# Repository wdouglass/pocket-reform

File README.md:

# MNT Pocket Reform (Research Project)

## License

Copyright 2021 MNT Research GmbH.

The following licenses are used in the project, unless specified differently in a particular subfolder:

- Schematics, PCBs: [CERN-OHL-S v2](https://www.ohwr.org/project/cernohl/wikis/uploads/002d0b7d5066e6b3829168730237bddb/cern_ohl_s_v2.txt)
- Other documentation, artwork, photos and drawings that are not trademarks (see below): [CC-BY-SA 4.0](https://creativecommons.org/licenses/by-sa/4.0/legalcode)
- Software, firmware: Various. [GPL 3.0](https://www.gnu.org/licenses/gpl-3.0.en.html) if not specified otherwise in the file/subdirectory.

The "MNT" and "MNT REFORM" logos are trademarks of MNT Research GmbH. You may not use these in derived works. The reason for this is that we cannot be responsible for regulatory issues with derived boards and we cannot support them. If someone sees an MNT brand on a product, it has to be clear that it comes from MNT Research and not from a third party.

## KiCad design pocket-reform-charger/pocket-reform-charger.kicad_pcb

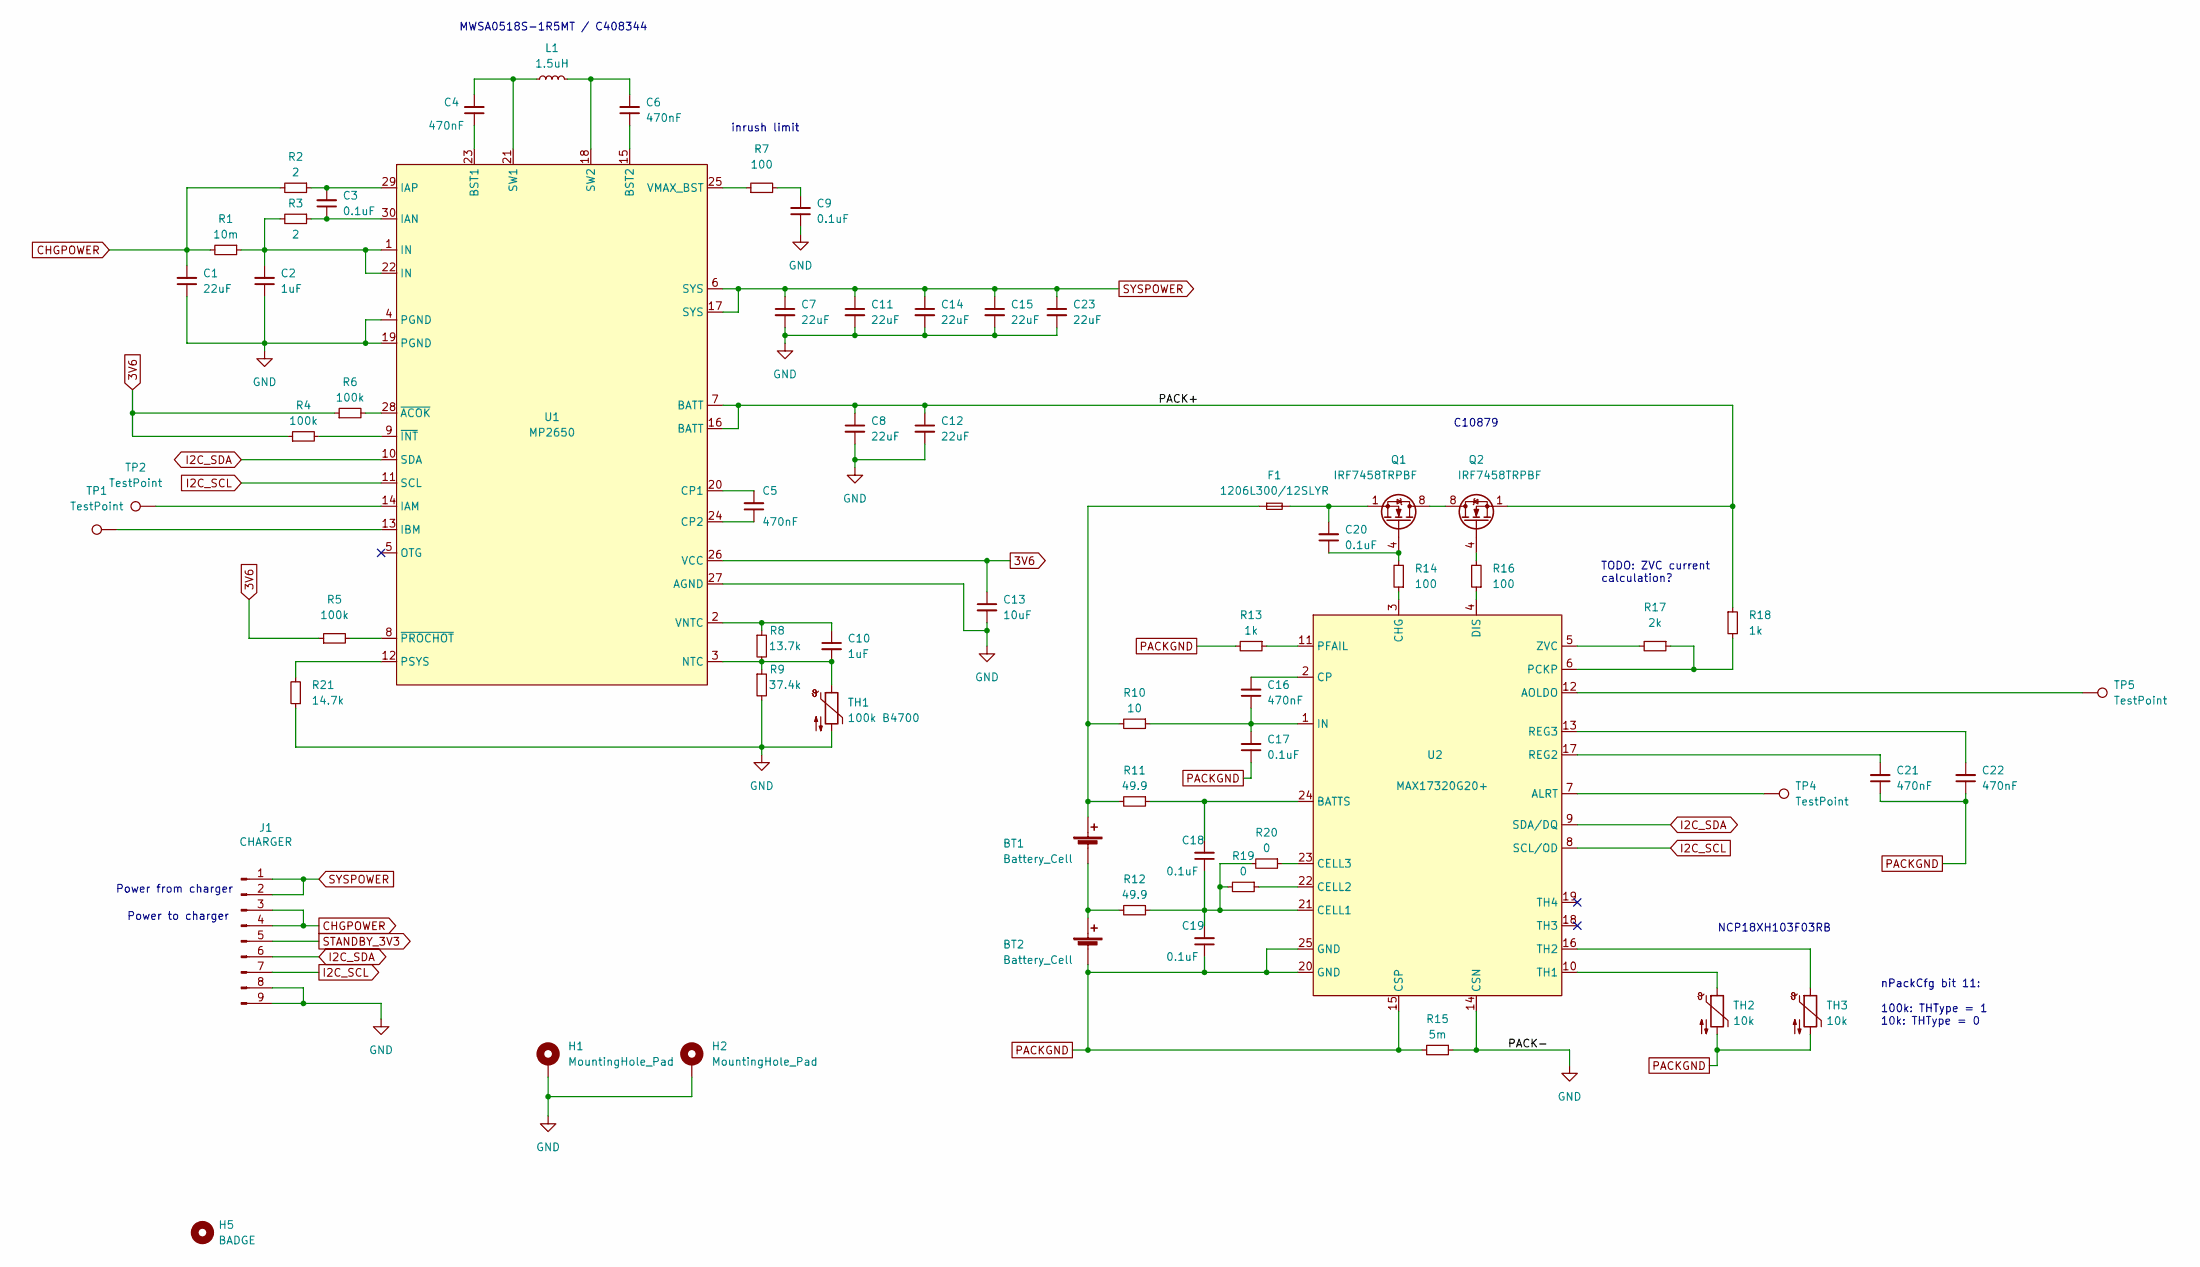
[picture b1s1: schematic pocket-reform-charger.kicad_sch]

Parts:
BT1, BT2: Battery_Cell; JST_PH_S2B-PH-SM4-TB_1x02-1MP_P2.00mm_Horizontal; LCSC C295747
C1, C7, C8, C11, C12, C14, C15, C23: 22uF; C_0805_2012Metric; LCSC C86816
C2, C10: 1uF; C_0603_1608Metric; LCSC C15849
C3, C9, C17, C18, C19, C20: 0.1uF; C_0603_1608Metric; LCSC C385964
C4, C5, C6, C16, C21, C22: 470nF; C_0603_1608Metric; LCSC C2905413
C13: 10uF; C_0603_1608Metric; LCSC C386081
F1: 1206L300/12SLYR; Fuse_1206_3216Metric; LCSC C1512043
H1, H2: MountingHole_Pad; MountingHole_2.2mm_M2_Pad
H5: BADGE; pocket-reform-charger-badge
J1: CHARGER; JST_PH_S9B-PH-SM4-TB_1x09-1MP_P2.00mm_Horizontal; LCSC C278795
L1: 1.5uH; L_Sunlord_MWSA0518_5.4x5.2mm; LCSC C408344
Q1, Q2: IRF7458TRPBF; SOIC-8_3.9x4.9mm_P1.27mm; LCSC C10879
R1: 10m; R_1206_3216Metric; LCSC C2961483
R2, R3: 2; R_0603_1608Metric; LCSC C403469
R4, R5, R6: 100k; R_0603_1608Metric; LCSC C189597
R7, R14, R16: 100; R_0603_1608Metric; LCSC C384296
R8: 13.7k; R_0603_1608Metric; LCSC C203293
R9: 37.4k; R_0603_1608Metric; LCSC C203565
R10: 10; R_0603_1608Metric; LCSC C193335
R11, R12: 49.9; R_0603_1608Metric; LCSC C403255
R13, R18: 1k; R_0603_1608Metric; LCSC C112433
R15: 5m; R_1206_3216Metric; LCSC C2937388
R17: 2k; R_0603_1608Metric; LCSC C163843
R19, R20: 0; R_0603_1608Metric
R21: 14.7k; R_0603_1608Metric; LCSC C100775
TH1: 100k B4700; R_0603_1608Metric; LCSC C153015
TH2, TH3: 10k; R_0603_1608Metric; LCSC C13564
TP1, TP2, TP4, TP5: TestPoint; TestPoint_Pad_1.0x1.0mm
U1: MP2650; MP2762A
U2: MAX17320G20+; QFN-24-1EP_4x4mm_P0.5mm_EP2.65x2.65mm_ThermalVias

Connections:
3V6: C13.1, R4.1, R5.1, R6.1, U1.26 (VCC)
/PACK+: C8.1, C12.1, Q2.1 (S), Q2.2 (S), Q2.3 (S), R18.1, U1.7 (BATT), U1.16 (BATT)
CHGPOWER: C1.2, J1.3, J1.4, R1.2, R2.2
GND: C1.1, C2.1, C7.2, C8.2, C9.1, C11.2, C12.2, C13.2, C14.2, C15.2, C23.2, H1.1, H2.1, J1.8, J1.9, R9.2, R15.1, R21.1, TH1.2, U1.4 (PGND), U1.19 (PGND), U1.27 (AGND), U2.14 (CSN)
I2C_SCL: J1.7, U1.11 (SCL), U2.8 (SCL/OD)
I2C_SDA: J1.6, U1.10 (SDA), U2.9 (SDA/DQ)
unnamed: BT1.1 (+), F1.1, R10.2, R11.2
unnamed: BT1.2 (-), BT2.1 (+), R12.2
unnamed: C2.2, R1.1, R3.2, U1.1 (IN), U1.22 (IN)
unnamed: C9.2, R7.2
unnamed: C20.2, F1.2, Q1.1 (S), Q1.2 (S), Q1.3 (S)
unnamed: Q1.5 (D), Q1.6 (D), Q1.7 (D), Q1.8 (D), Q2.5 (D), Q2.6 (D), Q2.7 (D), Q2.8 (D)
unnamed: C20.1, Q1.4 (G), R14.2
unnamed: Q2.4 (G), R16.2
unnamed: C4.1, U1.23 (BST1)
unnamed: C6.1, U1.15 (BST2)
unnamed: C5.2, U1.20 (CP1)
unnamed: C5.1, U1.24 (CP2)
unnamed: TP2.1, U1.14 (IAM)
unnamed: C3.1, R3.1, U1.30 (IAN)
unnamed: C3.2, R2.1, U1.29 (IAP)
unnamed: TP1.1, U1.13 (IBM)
unnamed: C10.2, R8.2, R9.1, TH1.1, U1.3 (NTC)
unnamed: R21.2, U1.12 (PSYS)
unnamed: C4.2, L1.1, U1.21 (SW1)
unnamed: C6.2, L1.2, U1.18 (SW2)
unnamed: R7.1, U1.25 (VMAX_BST)
unnamed: C10.1, R8.1, U1.2 (VNTC)
unnamed: R6.2, U1.28 (~ACOK)
unnamed: R4.2, U1.9 (~INT)
unnamed: R5.2, U1.8 (~PROCHOT)
unnamed: TP4.1, U2.7 (ALRT)
unnamed: TP5.1, U2.12 (AOLDO)
unnamed: C18.2, R11.1, U2.24 (BATTS)
unnamed: C18.1, C19.2, R12.1, R19.2, R20.2, U2.21 (CELL1)
unnamed: R19.1, U2.22 (CELL2)
unnamed: R20.1, U2.23 (CELL3)
unnamed: R14.1, U2.3 (CHG)
unnamed: C16.2, U2.2 (CP)
unnamed: R16.1, U2.4 (DIS)
unnamed: C16.1, C17.2, R10.1, U2.1 (IN)
unnamed: R17.1, R18.2, U2.6 (PCKP)
unnamed: R13.1, U2.11 (PFAIL)
unnamed: C21.2, U2.17 (REG2)
unnamed: C22.2, U2.13 (REG3)
unnamed: TH2.1, U2.10 (TH1)
unnamed: TH3.1, U2.16 (TH2)
unnamed: R17.2, U2.5 (ZVC)
PACKGND: BT2.2 (-), C17.1, C19.1, C21.1, C22.1, R13.2, R15.2, TH2.2, TH3.2, U2.15 (CSP), U2.20 (GND), U2.25 (GND)
STANDBY_3V3: J1.5
SYSPOWER: C7.1, C11.1, C14.1, C15.1, C23.1, J1.1, J1.2, U1.6 (SYS), U1.17 (SYS)

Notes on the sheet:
MWSA0518S-1R5MT / C408344
TODO: ZVC current calculation?
C10879
NCP18XH103F03RB
inrush limit
Power from charger
nPackCfg bit 11: 100k: THType = 1 10k: THType = 0
Power to charger

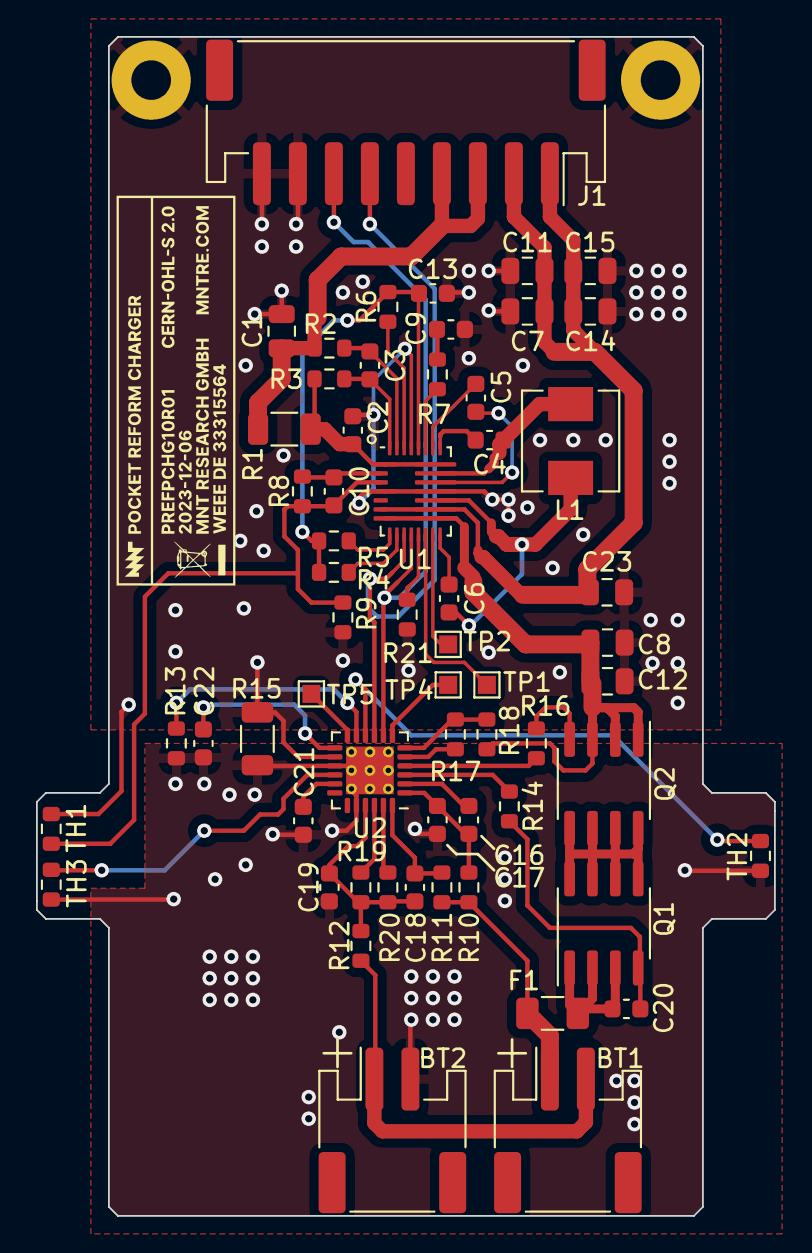
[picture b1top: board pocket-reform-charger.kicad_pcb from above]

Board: 2 copper layers, 41.0 x 65.5 mm, 63 parts (0 on the bottom side), 50 nets.

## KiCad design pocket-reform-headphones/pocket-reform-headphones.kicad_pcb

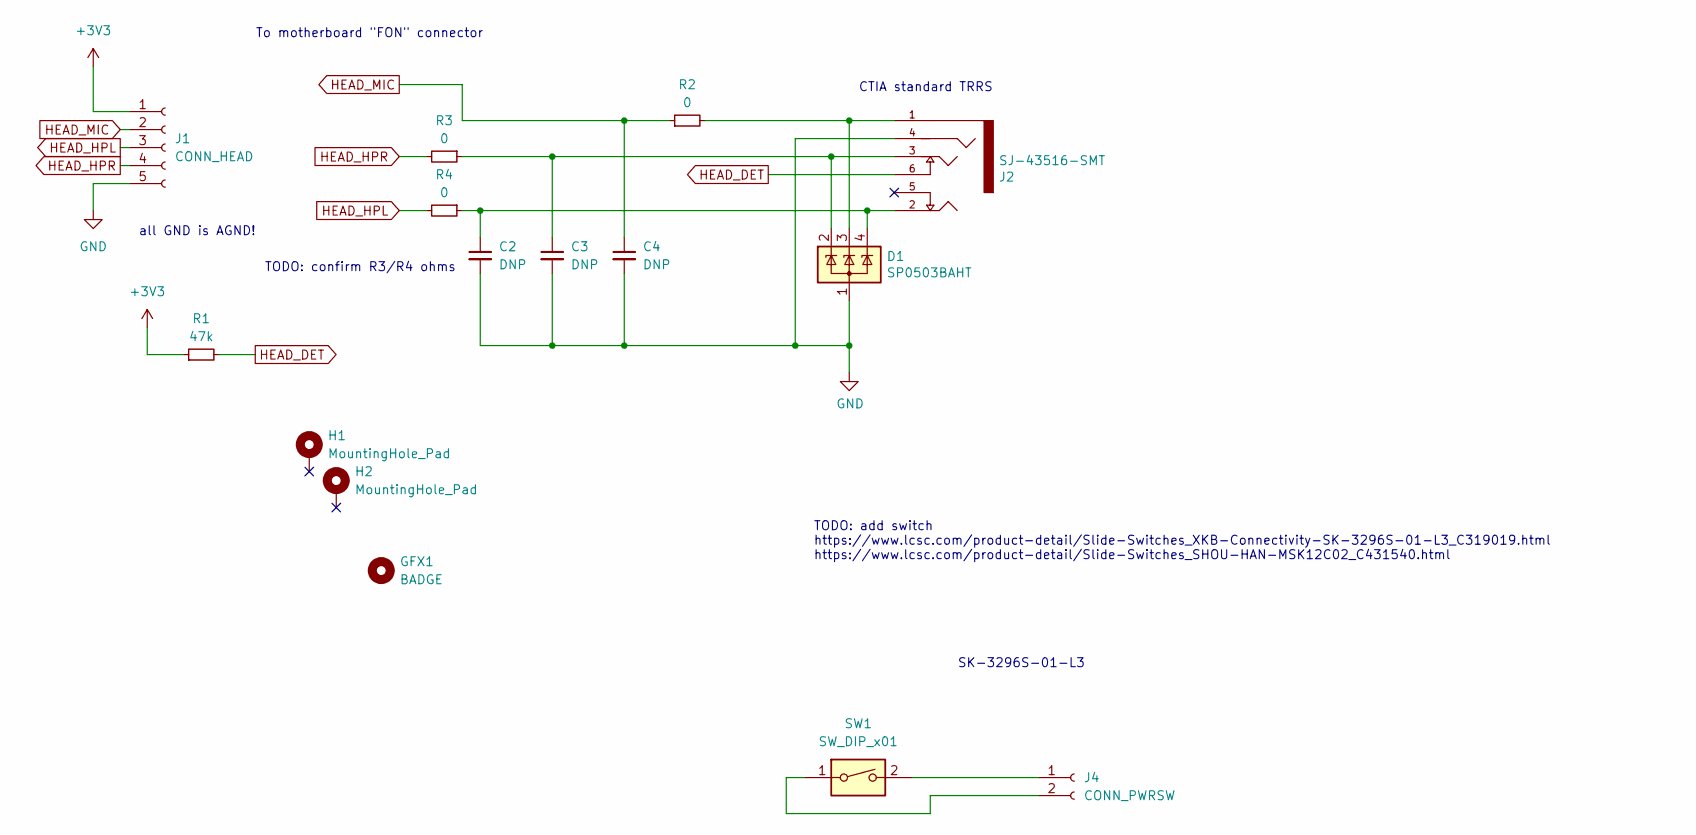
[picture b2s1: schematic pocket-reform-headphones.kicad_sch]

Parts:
C2, C3, C4: DNP; C_0603_1608Metric; LCSC DNP
D1: SP0503BAHT; SOT-143; LCSC C3040626
GFX1: BADGE; pref-headset-badge
H1, H2: MountingHole_Pad; MountingHole_2.2mm_M2_DIN965_Pad
J1: CONN_HEAD; JST_SH_SM05B-SRSS-TB_1x05-1MP_P1.00mm_Horizontal; LCSC C136657
J2: SJ-43516-SMT
J4: CONN_PWRSW; JST_SH_SM02B-SRSS-TB_1x02-1MP_P1.00mm_Horizontal; LCSC C160402
R1: 47k; R_0603_1608Metric
R2, R3, R4: 0; R_0603_1608Metric
SW1: SW_DIP_x01; SW_SPDT_PCM12; LCSC C319019

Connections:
+3V3: J1.1, R1.1
GND: C2.2, C3.2, C4.2, D1.1 (A), J1.5, J2.4 (RING2)
HEAD_DET: J2.6 (RING_SWITCH), R1.2
HEAD_HPL: J1.3, R4.2
HEAD_HPR: J1.4, R3.2
HEAD_MIC: C4.1, J1.2, R2.1
unnamed: C3.1, D1.2 (K), J2.3 (RING1), R3.1
unnamed: D1.3 (K), J2.1 (SLEEVE), R2.2
unnamed: C2.1, D1.4 (K), J2.2 (TIP), R4.1
unnamed: J4.1, SW1.2
unnamed: J4.2, SW1.1

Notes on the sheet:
SK-3296S-01-L3
To motherboard "FON" connector
TODO: add switch https://www.lcsc.com/product-detail/Slide-Switches_XKB-Connectivity-SK-3296S-01-L3_C319019.html https://www.lcsc.com/product-detail/Slide-Switches_SHOU-HAN-MSK12C02_C431540.html
all GND is AGND!
CTIA standard TRRS
TODO: confirm R3/R4 ohms

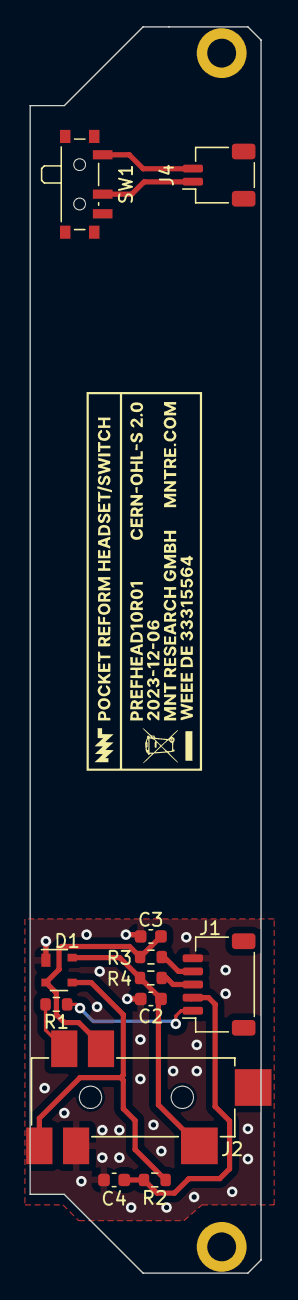
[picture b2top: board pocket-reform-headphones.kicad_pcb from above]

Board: 2 copper layers, 17.6 x 95.0 mm, 15 parts (0 on the bottom side), 11 nets.

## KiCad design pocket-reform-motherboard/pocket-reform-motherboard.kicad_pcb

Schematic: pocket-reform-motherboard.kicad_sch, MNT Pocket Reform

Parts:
BT1: V364; BatteryHolder_Keystone_2998_1x6.8mm
C2, C4, C5, C6, C17, C39, C51, C56, C65, C67: 10uF; C_0603_1608Metric
C7, C8, C11, C12, C18, C19, C52, C58: 10nF; C_0603_1608Metric
C9, C10, C20, C26, C34, C36: 1uF; C_0603_1608Metric
C13: 12pF; C_0603_1608Metric
C14, C83, C123, C124, C126: 47uF; C_0603_1608Metric
C15, C16: 330uF; CP_Elec_6.3x5.4
C21, C23: 18pF; C_0603_1608Metric
C22, C24: 27pF; C_0603_1608Metric; LCSC C107045
C25, C27, C28, C29, C30, C31, C32, C33, C35, C38, C40, C41, C42, C43, C44, C45, C46, C47, C48, C49, C50, C53, C54, C55, C57, C59, C60, C61, C62, C63, C64, C66, C68, C69, C72, C73, C76, C77, C78, C85, C86, C87, C88, C89, C90, C91, C92, C93: 0.1uF; C_0603_1608Metric
C37: 1nF; C_0603_1608Metric
C82: 470nF; C_0603_1608Metric
D1: LED_MODEM; LED_0603_1608Metric
D2, D4, D5, D6: PMEG3050EP,115; D_SOD-128
D7: BZX84-C5V6,215; D_SOD-323
D8, D9: LED_Small; LED_0603_1608Metric
D10: 19-337/R6GHBHC-A01/2T; LED_19-337_R6GHBHC-A01_2T
D11: SS54?; D_SMA
D12: SD0603S040S0R2; D_0603_1608Metric
D23: LED_NVME; LED_0603_1608Metric
FB1: 220@100MHz 1.4A; L_0603_1608Metric
FB2, FB3, FB4, FB5, FB8, FB9, FB10: 100@100MHz 3A; L_0603_1608Metric
GFX1: MountingHole; pocket-reform
H1, H2, H3, H4: MountingHole_Pad; MountingHole_2.2mm_M2_DIN965_Pad
H5, H6, H7: NGFF-Mount1; WA-SMSI-M2
J1: CHARGER; JST_PH_S9B-PH-SM4-TB_1x09-1MP_P2.00mm_Horizontal
J2: DM3AT-SF-PEJM5; LCSC C114218
J3, J14: USB_C_Receptacle; USB_C_Receptacle_Amphenol_12401548E4-2A_CircularHoles
J4: 09452812561; Manufacturer_Part_Number 09452812561; Mouser Part Number 617-09452812561
J5: SYSCTL; JST_PH_S4B-PH-SM4-TB_1x04-1MP_P2.00mm_Horizontal
J6: USB_INT1; JST_PH_S4B-PH-SM4-TB_1x04-1MP_P2.00mm_Horizontal
J7: HDMI_D_1.4; HDMI_Micro-D_Molex_46765-0x01
J8: SIM_Card; MOLEX_78800-0001
J9: USB_C_Receptacle_USB2.0; USB_C_Receptacle_HRO_TYPE-C-31-M-12
J10: 1-2199230-6; TE_1-2199230-6
J11: Conn_01x33; Hirose_FH12-33S-0.5SH_1x33-1MP_P0.50mm_Horizontal
J12: 2199230-5; TE_2199230-5
J13: FH35C-31S-0.3HW(50); TE_3-2328724-1
J15: Conn_01x02; JST_GH_SM02B-GHS-TB_1x02-1MP_P1.25mm_Horizontal
J16, J17: Conn_01x03; PinHeader_1x03_P2.54mm_Vertical
L1: 22uH; L_Taiyo-Yuden_NR-30xx
L2: 2.2uH; L_1210_3225Metric
L3, L4: 15uH; L_Vishay_IHLP-4040
L5, L6: 15uH; L_Taiyo-Yuden_NR-30xx; LCSC C223122
MK1: MP23ABS1TR; MIC_MP23ABS1TR; PARTREV 5
R1, R29, R34, R36, R58, R60, R61, R110: 1k; R_0603_1608Metric
R4, R5, R9, R11, R12, R13, R44, R45, R46, R49, R50, R51, R67, R70, R71, R81, R83, R84, R101, R102, R103, R104, R105, R106, R107, R108, R109, R111: 0; R_0603_1608Metric
R6, R7, R8, R69, R87: 100k; R_0603_1608Metric
R10, R27, R55: 200k; R_0603_1608Metric
R14: 280k; R_0603_1608Metric
R15, R17, R22, R30, R32, R38, R52, R54, R56, R68, R75, R85, R96: 10k; R_0603_1608Metric
R16: 3.16k; R_0603_1608Metric
R18: 5.83k; R_0603_1608Metric
R19: 1.3M; R_0603_1608Metric
R20: 300k; R_0603_1608Metric
R21: 1M; R_0603_1608Metric
R23, R62, R63, R64: DNP; R_0603_1608Metric
R24, R25, R26, R89, R93: 4.7k; R_0603_1608Metric
R28: 120k; R_0603_1608Metric
R31, R33: 36k; R_0603_1608Metric
R35: 1k; R_0603_1608Metric; LCSC C105428
R37, R39, R40, R41: 75 1%; R_0603_1608Metric
R47, R48: 27.4; R_0603_1608Metric
R53: 12k 1%; R_0603_1608Metric
R57, R59: 4.7k; R_0603_1608Metric; LCSC C105428
R65, R66, R198, R199: 49.9; R_0603_1608Metric
R72: 2k2; R_0603_1608Metric
R76, R77, R79, R80, R82: 33; R_0603_1608Metric
R90: 27k; R_0603_1608Metric
R97, R98, R99, R100: 47k; R_0603_1608Metric
SW1: SW_DIP_x01; SW_DIP_SPSTx01_Slide_Omron_A6S-110x_W8.9mm_P2.54mm
SW2: RESET; SW_Push_1P1T_NO_CK_KMR2
TP1: PRTCTL1; TestPoint_Pad_D1.0mm
TP2: PRTCTL3; TestPoint_Pad_D1.0mm
TP3: PRTCTL2; TestPoint_Pad_D1.0mm
TP4: PRTCTL4; TestPoint_Pad_D1.0mm
TP5, TP6: TestPoint; TestPoint_Pad_D1.0mm; LCSC DNP
TR1: TG111-MSC13LF; Transformer_Ethernet_HALO_TG111-MSC13
U1: reform2-som-connector; TE_1473149-4
U2: MAX1837EUT33+T; SOT-23-6
U3: LM3674MFX-ADJ/NOPB; SOT-23-5
U4: TLV1117-18; SOT-223
U5, U6: TPS5450DDAR; TI_SO-PowerPAD-8_ThermalVias
U7: CN301; SOT-23-5
U8: RP2040; RP2040-QFN-56
U9: USB7002/KDX; QFN40P1200X1200X90-101N; PARTREV N/A
U10: W25Q32JVSS; SOIC-8_5.23x5.23mm_P1.27mm
U11: PCF8523T; SOIC-8_3.9x4.9mm_P1.27mm
U12: AP22815; SOT-23-5
U13: TXS0108EPW; TSSOP-20_4.4x6.5mm_P0.65mm
U14: SN74AVC1T45; SOT-23-6
U15, U16, U19, U20, U21, U22: TPD4E02B04DQA; USON-10_2.5x1.0mm_P0.5mm
U17: TPD12S521; TSSOP50P640X120-38N
U18: TLV320AIC3100; VQFN-32-1EP_5x5mm_P0.5mm_EP3.5x3.5mm
U23: FUSB302BMPX; WQFN-14-1EP_2.5x2.5mm_P0.5mm_EP1.45x1.45mm
Y1: 25MHz; Crystal_SMD_Abracon_ABM8G-4Pin_3.2x2.5mm
Y2: 12MHz 18pF; Crystal_SMD_3225-4Pin_3.2x2.5mm; LCSC C91749
Y3: 32.768 kHz; Crystal_SMD_3215-2Pin_3.2x1.5mm

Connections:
1V2_ENABLE: R8.1, R46.2, U3.3 (EN)
3V3_ENABLE: R7.1, R49.2, U6.5 (EN)
5V_ENABLE: R6.1, R51.2, U5.5 (EN)
+1V1: C26.1, C28.1, C30.1, U8.23 (DVDD), U8.45 (VREG_VOUT), U8.50 (DVDD)
+1V2: C13.1, C17.1, L2.2, R14.1, U9.9 (VDD12), U9.18 (VDD12), U9.25 (VDD12), U9.33 (VDD12), U9.41 (VDD12), U9.55 (VDD12), U9.78 (VDD12), U9.83 (VDD12), U9.93 (VDD12)
+1V8: C10.1, C56.1, C62.1, J13.31, R71.2, R81.2, U4.2 (VO), U18.3 (DVDD)
+3V3: C6.1, C16.1, C19.2, C69.2, C77.1, FB3.1, FB4.1, FB5.2, FB8.1, J13.1, J13.2, J13.3, J13.4, J13.26, J13.27, L4.2, MK1.5 (VDD), R4.2, R17.1, R22.1, R25.1, R29.1, R30.1, R31.1, R32.1, R33.1, R34.1, R52.2, R54.2, R85.1, R87.1, R90.1, R97.2, R98.2, R99.2, R100.2, U3.1 (Vin), U9.26 (VDD33), U9.44 (VDD33), U9.53 (VDD33), U9.62 (VDD33), U9.67 (VDD33), U9.79 (VDD33), U9.86 (VDD33), U9.99 (VDD33)
+5V: C15.1, C18.2, C40.1, C47.1, C73.2, D12.2 (A), FB1.1, FB2.1, J3.A4 (VBUS), J3.A9 (VBUS), J3.B4 (VBUS), J3.B9 (VBUS), L3.2, R11.1, R15.1, R62.2, R68.2, U1.1 (5V), U1.2 (5V), U1.3 (5V), U1.4 (5V), U1.5 (5V), U1.6 (5V), U8.48 (USB_VDD), U12.5 (IN), U17.1 (5V_SUPPLY)
/DP1_DISCHARGE: U9.46 (PF5)
/DP1_VCONN1: U9.49 (PF8)
/DP1_VCONN2: U9.50 (PF9)
/DP2_DISCHARGE: U9.45 (PF4)
/DP2_VCONN1: U9.51 (PF10)
/DP2_VCONN2: U9.52 (PF11)
/GPIO90: U9.75 (PF26)
/GPIO91: U9.76 (PF27)
/GPIO92: U9.77 (PF28)
/GPIO93: U9.74 (PF29)
/GPIO94: R54.1, U9.2 (PF30/VBUS_DET)
/GPIO95: U9.3 (PF31)
/M2_CLKREQn: J10.52
/M2_SMB_ALERTn: J10.44
/M2_SMB_CLK: J10.40
/M2_SMB_DATA: J10.42
/M_ANTCTL0: J12.59
/M_ANTCTL1: J12.61
/M_ANTCTL2: J12.58
/M_ANTCTL3: J12.56
/M_COEX1: J12.64
/M_COEX2: J12.62
/M_CONFIG_0: J12.21
/M_CONFIG_1: J12.69
/M_CONFIG_2: J12.75
/M_CONFIG_3: J12.1
/M_DPR: J12.25
/M_I2C_SCL: J12.38
/M_I2C_SDA: J12.68
/M_I2S_CLK: J12.20
/M_I2S_MCLK(IO): J12.60
/M_I2S_RX: J12.22
/M_I2S_TX: J12.24
/M_I2S_WA: J12.28
/M_LAA_TX_EN: J12.63
/M_SIM1_DET: J12.66
/M_SIM2_CLK: J12.44
/M_SIM2_DATA: J12.42
/M_SIM2_DET: J12.40
/M_SIM2_PWR: J12.48
/M_SIM2_RESET: J12.46
/M_VIO_1V8: J12.65
/PRT_CTL1: TP1.1, U9.60 (PF17)
/PRT_CTL2: TP3.1, U9.58 (PF15)
/PRT_CTL3: TP2.1, U9.59 (PF16)
/PRT_CTL4: TP4.1, U9.56 (PF13)
/RUD+: J9.A6 (D+), J9.B6 (D+), R47.2, R63.1
/RUD-: J9.A7 (D-), J9.B7 (D-), R48.2, R64.1
/U_GPIO70: U9.47 (PF6)
/U_GPIO71: U9.48 (PF7)
/U_GPIO76: U9.54 (PF12)
/U_GPIO78: U9.57 (PF14)
/U_M_I2C_CLK: U9.61 (PF18)
/U_M_I2C_DATA: U9.66 (PF19)
/U_SPI_CE_N: U9.69 (PF20/CFG_NON_REM)
/U_SPI_CLK: U9.68 (PF21)
/U_SPI_D0: R55.1, U9.70 (PF22/CFG_BC_EN)
/U_SPI_D1: U9.71 (PF23)
/U_SPI_D2: U9.72 (PF24)
/U_SPI_D3: U9.73 (PF25)
/~M_LED1: D1.1 (K), J12.10
/~M_PWROFF: J12.6
/~M_WOWWAN: J12.23
/~M_W_DISABLE1: J12.8
/~M_W_DISABLE2: J12.26
/~PCIE2_CLKREQ: J12.52
/~PCIE2_WAKE: J12.54
BACKLIGHT_EN: J13.6
BACKLIGHT_PWM: U1.164 (SPDIF_RX/PWM2)
DAC_BCLK: R76.1, U1.170 (SAI2_TXC)
DAC_DIN: R79.1, U1.166 (SAI2_RXD)
DAC_DOUT: R77.1, U1.178 (SAI2_TXD)
DAC_MCLK: R82.2, U1.176 (SAI2_MCLK)
DAC_RXFS: U1.168 (SAI2_RXFS)
DAC_SCL: U1.101 (I2C3_SCL), U11.6 (SCL), U18.10 (SCL)
DAC_SDA: U1.103 (I2C3_SDA), U11.5 (SDA), U18.9 (SDA)
DAC_TXFS: R80.1, U1.172 (SAI2_TXFS)
DISP_EN: J13.30
DISP_TE: J13.25
DSI_CLK_N: J11.19, J13.15
DSI_CLK_P: J11.20, J13.16
DSI_D0_N: J11.25, J13.12
DSI_D0_P: J11.26, J13.13
DSI_D1_N: J11.22, J13.18
DSI_D1_P: J11.23, J13.19
DSI_D2_N: J11.16, J13.21
DSI_D2_P: J11.17, J13.22
DSI_D3_N: J11.13, J13.9
DSI_D3_P: J11.14, J13.10
ETH0_A+: TR1.2 (TD1+), U1.29 (TRX0_P)
ETH0_A-: TR1.3 (TD1-), U1.27 (TRX0_N)
ETH0_B+: TR1.5 (TD2+), U1.23 (TRX1_P)
ETH0_B-: TR1.6 (TD2-), U1.21 (TRX1_N)
ETH0_C+: TR1.8 (TD3+), U1.17 (TRX2_P)
ETH0_C-: TR1.9 (TD3-), U1.15 (TRX2_N)
ETH0_D+: TR1.11 (TD4+), U1.11 (TRX3_P)
ETH0_D-: TR1.12 (TD4-), U1.9 (TRX3_N)
ETH0_DA+: J4.1, TR1.23 (MTX1+)
ETH0_DA-: J4.2, TR1.22 (MTX1-)
ETH0_DB+: J4.6, TR1.20 (MTX2+)
ETH0_DB-: J4.7, TR1.19 (MTX2-)
ETH0_DC+: J4.4, TR1.17 (MTX3+)
ETH0_DC-: J4.5, TR1.16 (MTX3-)
ETH0_DD+: J4.9, TR1.14 (MX4+)
ETH0_DD-: J4.10, TR1.13 (MX4-)
ETH0_LED_LINK1: D9.1 (K), U1.83 (JTAG_TDO)
ETH0_LED_RX: D8.1 (K), U1.79 (JTAG_MOD)
HDMI_AUXN: U1.189 (HDMI_AUX_N)
HDMI_AUXP: U1.187 (HDMI_AUX_P)
HDMI_CEC: R100.1, U1.197 (HDMI_CEC), U17.16 (CE_REMOTE_IN)
HDMI_CLKN: J7.14 (CK-), U1.163 (HDMI_CLK_N), U17.15 (TMDS_CK-), U17.24 (TMDS_CK-)
HDMI_CLKP: J7.12 (CK+), U1.165 (HDMI_CLK_P), U17.13 (TMDS_CK+), U17.26 (TMDS_CK+)
HDMI_HPD: R97.1, U1.199 (HDMI_HPD), U17.19 (HOTPLUG_DET_IN)
HDMI_SCL: R98.1, U1.195 (HDMI_DDC_SCL), U17.17 (DDC_CLK_IN)
HDMI_SDA: R99.1, U1.193 (HDMI_DDC_SDA), U17.18 (DDC_DAT_IN)
HDMI_TX0N: J7.11 (D0-), U1.169 (HDMI_TX0_N), U17.12 (TMDS_D0-), U17.27 (TMDS_D0-)
HDMI_TX0P: J7.9 (D0+), U1.171 (HDMI_TX0_P), U17.10 (TMDS_D0+), U17.29 (TMDS_D0+)
HDMI_TX1N: J7.8 (D1-), U1.175 (HDMI_TX1_N), U17.9 (TMDS_D1-), U17.30 (TMDS_D1-)
HDMI_TX1P: J7.6 (D1+), U1.177 (HDMI_TX1_P), U17.7 (TMDS_D1+), U17.32 (TMDS_D1+)
HDMI_TX2N: J7.5 (D2-), U1.181 (HDMI_TX2_N), U17.6 (TMDS_D2-), U17.33 (TMDS_D2-)
HDMI_TX2P: J7.3 (D2+), U1.183 (HDMI_TX2_P), U17.4 (TMDS_D2+), U17.35 (TMDS_D2+)
IMX_RESETn: U1.87 (EXT_RESET_N)
IMX_RTC_IRQ: R67.1, U1.141 (RTC_IRQ)
IMX_UART1_RX: J16.2, U1.126 (UART1_RXD)
IMX_UART1_TX: J16.1, U1.128 (UART1_TXD)
IMX_UART2_RX: J17.2, U1.122 (UART2_RXD)
IMX_UART2_TX: J17.1, U1.124 (UART2_TXD)
IMX_WAKE: R45.2, U1.145 (GPIO1_IO3)
LPC_MISO: R50.2, U1.93 (ECSPI2_MISO)
LPC_MOSI: R44.2, U1.91 (ECSPI2_MOSI)
LPC_SCK: U1.97 (ECSPI2_SCLK), U8.13 (GPIO10)
LPC_SS0: U1.89 (ECSPI2_SS0), U8.12 (GPIO9)
M2B_RST: J12.67
unnamed: BT1.1 (+), U11.3 (VBAT)
unnamed: C9.1, R4.1, U4.3 (VI)
unnamed: C11.1, U5.1 (BOOT)
unnamed: C11.2, D5.1 (K), L3.1, U5.8 (PH)
unnamed: C12.1, U6.1 (BOOT)
unnamed: C12.2, D6.1 (K), L4.1, U6.8 (PH)
unnamed: C13.2, R10.1, R14.2, U3.4 (FB)
unnamed: C20.1, D7.1 (K), R21.1, U7.2 (VCC)
unnamed: C21.1, U9.97 (XTALO), Y1.1
unnamed: C22.1, U8.20 (XIN), Y2.1
unnamed: C23.1, U9.98 (XTALI/CLK_IN), Y1.3
unnamed: C24.1, R35.1, Y2.3
unnamed: C37.1, R37.2, R39.2, R40.2, R41.2
unnamed: C39.1, C41.1, FB1.2, J6.1
unnamed: C42.1, TR1.1 (TCT1)
unnamed: C43.1, TR1.4 (TCT2)
unnamed: C44.1, TR1.7 (TCT3)
unnamed: C45.1, TR1.10 (TCT4)
unnamed: C48.1, C49.1, R75.1, R81.1, U13.2 (VCCA), U14.1 (VCCA)
unnamed: C50.1, C51.1, FB5.1, U18.17 (AVDD), U18.28 (HPVDD)
unnamed: C57.1, C67.1, FB2.2, U18.21 (SPKVDD), U18.24 (SPKVDD)
unnamed: C63.1, C64.1, C65.1, C66.1, FB8.2, J2.4 (VDD), U13.19 (VCCB), U14.6 (VCCB)
unnamed: C68.1, U18.14 (MIC1RP)
unnamed: C68.2, MK1.1 (OUT), R72.2, U18.11 (VOL/MICDET)
unnamed: C72.2, U17.37 (ESD_BYP)
unnamed: C76.1, C82.1, J15.1, L5.2
unnamed: C78.1, C82.2, J15.2, L6.2
unnamed: C85.1, J3.A3 (TX1-), U20.4 (IO3)
unnamed: C86.1, J3.B3 (TX2-), U22.4 (IO3)
unnamed: C87.1, J7.19 (+5V), U17.38 (5V_OUT)
unnamed: C88.1, J3.A2 (TX1+), U20.5 (IO4)
unnamed: C89.1, J3.B2 (TX2+), U22.5 (IO4)
unnamed: C90.1, J14.A3 (TX1-), U19.4 (IO3)
unnamed: C91.1, J14.B3 (TX2-), U21.4 (IO3)
unnamed: C92.1, J14.A2 (TX1+), U19.5 (IO4)
unnamed: C93.1, J14.B2 (TX2+), U21.5 (IO4)
unnamed: C52.1, C53.1, C54.1, C55.1, C83.1, C123.1, FB3.2, J12.2, J12.4, J12.70, J12.72, J12.74, R1.1
unnamed: C58.1, C59.1, C60.1, C61.1, C124.1, C126.1, FB4.2, J10.2, J10.4, J10.12, J10.14, J10.16, J10.18, J10.70, J10.72, J10.74, R110.1
unnamed: D1.2 (A), R1.2
unnamed: D4.1 (K), L1.1, U2.4 (LX)
unnamed: D8.2 (A), R29.2
unnamed: D9.2 (A), R34.2
unnamed: D10.4 (BA), R61.2
unnamed: D10.5 (GA), R60.2
unnamed: D10.6 (RA), R58.2
unnamed: D12.1 (K), R89.1, R93.1
unnamed: D23.1 (K), J10.10
unnamed: D23.2 (A), R110.2
unnamed: FB9.1, U18.22 (SPKP), U18.26 (SPKP)
unnamed: FB9.2, L5.1
unnamed: FB10.1, U18.19 (SPKM), U18.23 (SPKM)
unnamed: FB10.2, L6.1
unnamed: J2.1 (DAT2), U13.20 (B1)
unnamed: J2.2 (DAT3/CD), U13.18 (B2)
unnamed: J2.3 (CMD), U13.14 (B6)
unnamed: J2.5 (CLK), U14.4 (B)
unnamed: J2.7 (DAT0), U13.13 (B7)
unnamed: J2.8 (DAT1), U13.12 (B8)
unnamed: J3.A5 (CC1), R83.1, U16.1 (IO1)
unnamed: J3.B5 (CC2), R84.1, U16.2 (IO2)
unnamed: J7.1 (HPD/HEAC-), R96.1, U17.20 (HOTPLUG_DET_OUT)
unnamed: J7.15 (CEC), R90.2, U17.23 (CE_REMOTE_OUT)
unnamed: J7.17 (SCL), R89.2, U17.22 (DDC_CLK_OUT)
unnamed: J7.18 (SDA), R93.2, U17.21 (DDC_DAT_OUT)
unnamed: J9.A4 (VBUS), J9.A9 (VBUS), J9.B4 (VBUS), J9.B9 (VBUS), R62.1
unnamed: J10.11, R107.1
unnamed: J10.13, R104.1
unnamed: J10.23, R108.1
unnamed: J10.25, R105.1
unnamed: J10.35, R109.1
unnamed: J10.37, R106.1
unnamed: J14.A5 (CC1), R101.2, R111.1, U15.1 (IO1)
unnamed: J14.B5 (CC2), R102.2, R103.1, U15.2 (IO2)
unnamed: L2.1, U3.5 (SW)
unnamed: R5.1, U9.1 (RESET_N)
unnamed: R9.1, U2.1 (FB)
unnamed: R11.2, U1.118 (USB1_VBUS)
unnamed: R12.2, U1.30 (UART3_TXD)
unnamed: R13.1, U1.32 (UART3_RXD)
unnamed: R15.2, R16.1, U5.4 (VSENSE)
unnamed: R17.2, R18.1, U6.4 (VSENSE)
unnamed: R19.1, R20.2, U7.4 (LBI)
unnamed: R22.2, R23.1, U9.21 (CFG_STRAP1)
unnamed: R24.1, U9.64 (TEST2)
unnamed: R25.2, U9.63 (TEST1)
unnamed: R26.1, U9.65 (TEST3)
unnamed: R27.1, U9.22 (CFG_STRAP2)
unnamed: R30.2, U9.4 (DP1_VBUS_MON)
unnamed: R31.2, U9.87 (CC1_UP)
unnamed: R32.2, U9.36 (DP2_VBUS_MON)
unnamed: R33.2, U9.88 (CC2_UP)
unnamed: R35.2, U8.21 (XOUT)
unnamed: R37.1, TR1.15 (MCT4)
unnamed: R39.1, TR1.18 (MCT3)
unnamed: R40.1, TR1.21 (MCT2)
unnamed: R41.1, TR1.24 (MTC1)
unnamed: R44.1, U8.11 (GPIO8)
unnamed: R45.1, U8.30 (GPIO19)
unnamed: R46.1, U8.35 (GPIO23)
unnamed: R47.1, U8.47 (USB_DP)
unnamed: R48.1, U8.46 (USB_DM)
unnamed: R49.1, U8.36 (GPIO24)
unnamed: R50.1, U8.14 (GPIO11)
unnamed: R51.1, U8.37 (GPIO25)
unnamed: R52.1, U9.80 (VBUS_MON_UP)
unnamed: R53.1, U9.100 (RBIAS)
unnamed: R58.1, U8.28 (GPIO17)
unnamed: R60.1, U8.27 (GPIO16)
unnamed: R61.1, U8.18 (GPIO15)
unnamed: R67.2, U11.7 (~INT1/CLKOUT)
unnamed: R68.1, U12.3 (FLG)
unnamed: R70.1, U18.31 (~RESET)
unnamed: R71.1, U18.2 (IOVDD)
unnamed: R72.1, U18.12 (MICBIAS)
unnamed: R75.2, U13.10 (OE), U14.5 (DIR)
unnamed: R76.2, U18.7 (BCLK)
unnamed: R77.2, U18.5 (DIN)
unnamed: R79.2, U18.4 (DOUT)
unnamed: R80.2, U18.6 (WCLK)
unnamed: R82.1, U18.8 (MCLK)
unnamed: R85.2, U17.2 (LV_SUPPLY)
unnamed: R103.2, U23.1 (CC2), U23.14 (CC2)
unnamed: R111.2, U23.10 (CC1), U23.11 (CC1)
unnamed: U11.1 (OSCI), Y3.1
unnamed: U11.2 (OSCO), Y3.2
PCIE1_CLK_N: J10.53, R199.2, U1.60 (PCIE1_REFCLK_N)
PCIE1_CLK_P: J10.55, R198.2, U1.58 (PCIE1_REFCLK_P)
PCIE1_RESETn: J10.50, U1.37 (PCIE_RST_B)
PCIE1_RXN: U1.54 (PCIE1_RX_N)
PCIE1_RXP: U1.52 (PCIE1_RX_P)
PCIE1_RX_N: J10.41
PCIE1_RX_P: J10.43
PCIE1_TXN: U1.48 (PCIE1_TX_N)
PCIE1_TXP: U1.46 (PCIE1_TX_P)
PCIE1_TX_N: J10.47
PCIE1_TX_P: J10.49
PCIE2_CLK_N: J12.53, R65.2, U1.66 (PCIE2_REFCLK_N)
PCIE2_CLK_P: J12.55, R66.2, U1.64 (PCIE2_REFCLK_P)
PCIE2_RESETn: J12.50, U1.24 (WIFI_RESET)
PCIE2_RX_N: J12.47, U1.78 (PCIE2_RX_N)
PCIE2_RX_P: J12.49, U1.76 (PCIE2_RX_P)
PCIE2_TX_N: J12.41, U1.72 (PCIE2_TX_N)
PCIE2_TX_P: J12.43, U1.70 (PCIE2_TX_P)
PROG: R36.1, SW1.1
QSPI_CS: R36.2, R38.2, U8.56 (QSPI_SS), U10.1 (~CS)
QSPI_SCK: U8.52 (QSPI_SCLK), U10.6 (CLK)
QSPI_SD0: U8.53 (QSPI_SD0), U10.5 (DI(IO0))
QSPI_SD1: U8.55 (QSPI_SD1), U10.2 (DO(IO1))
QSPI_SD2: U8.54 (QSPI_SD2), U10.3 (IO2)
QSPI_SD3: U8.51 (QSPI_SD3), U10.7 (IO3)
RESET: R56.2, SW2.1 (A), U8.26 (RUN)
RP_FUSB_INT: U8.17 (GPIO14), U23.5 (INT_N)
RP_SCL0: J1.7, R57.1, U8.3 (GPIO1), U23.6 (SCL)
RP_SDA0: J1.6, R59.1, U8.2 (GPIO0), U23.7 (SDA)
RP_UART1_RX: J5.3, U8.7 (GPIO5)
RP_UART1_TX: J5.2, U8.6 (GPIO4)
RP_UART2_RX: R12.1, U8.16 (GPIO13)
RP_UART2_TX: R13.2, U8.15 (GPIO12)
SD_CLK: U1.22 (SD2_CLK), U14.3 (A)
SD_CMD: U1.20 (SD2_CMD), U13.7 (A6)
SD_D0: U1.12 (SD2_DATA0), U13.8 (A7)
SD_D1: U1.14 (SD2_DATA1), U13.9 (A8)
SD_D2: U1.16 (SD2_DATA2), U13.1 (A1)
SD_D3: U1.18 (SD2_DATA3), U13.3 (A2)
SD_DET: J2.9 (DET_B), R87.2, U1.26 (SD2_CD)
STANDBY_3V3: C14.1, C25.1, C27.1, C29.1, C31.1, C32.1, C33.1, C34.1, C35.1, C36.1, C38.1, C46.2, J1.5, J5.1, L1.2, R38.1, R56.1, R57.2, R59.2, U2.6 (OUT), U8.1 (IOVDD), U8.10 (IOVDD), U8.22 (IOVDD), U8.33 (IOVDD), U8.42 (IOVDD), U8.43 (ADC_AVDD), U8.44 (VREG_IN), U8.49 (IOVDD), U10.8 (VCC), U11.8 (VDD), U23.3 (VDD), U23.4 (VDD)
SWC: TP6.1, U8.24 (SWCLK)
SWD: TP5.1, U8.25 (SWD)
UIM_CLK: J8.3 (CLK), J12.32
UIM_IO: J8.7 (I/O), J12.34
UIM_PWR: J8.1 (VCC), J12.36
UIM_RST: J8.2 (RST), J12.30
UIM_VPP: J8.6 (VPP)
USB1_DN: U1.100 (USB1_D_N), U9.90 (USB2UP_DM)
USB1_DP: U1.102 (USB1_D_P), U9.89 (USB2UP_DP)
USB1_RXN: U1.112 (USB1_RX_N), U9.95 (USB3UP_RXDMA)
USB1_RXP: U1.114 (USB1_RX_P), U9.94 (USB3UP_RXDPA)
USB1_TXN: U1.106 (USB1_TX_N), U9.92 (USB3UP_TXDMA)
USB1_TXP: U1.108 (USB1_TX_P), U9.91 (USB3UP_TXDPA)
USB2_DN: R64.2, U1.125 (USB2_D_N)
USB2_DP: R63.2, U1.127 (USB2_D_P)
USB2_RXN: J12.35, U1.121 (USB2_RX_N)
USB2_RXP: J12.37, U1.119 (USB2_RX_P)
USB2_TXN: J12.29, U1.115 (USB2_TX_N)
USB2_TXP: J12.31, U1.113 (USB2_TX_P)
USBH_1A_RXN: J3.B10 (RX1-), U9.11 (USB3DN_RXDM1A), U20.1 (IO1)
USBH_1A_RXP: J3.B11 (RX1+), U9.10 (USB3DN_RXDP1A), U20.2 (IO2)
USBH_1A_TXN: C85.2, U9.8 (USB3DN_TXDM1A)
USBH_1A_TXP: C88.2, U9.7 (USB3DN_TXDP1A)
USBH_1B_RXN: J3.A10 (RX2-), U9.17 (USB3DN_TXDM1B), U22.1 (IO1)
USBH_1B_RXP: J3.A11 (RX2+), U9.16 (USB3DN_TXDP1B), U22.2 (IO2)
USBH_1B_TXN: C86.2, U9.20 (USB3DN_RXDM1B)
USBH_1B_TXP: C89.2, U9.19 (USB3DN_RXDP1B)
USBH_1_CC1: R83.2, U9.12 (DP1_CC1)
USBH_1_CC2: R84.2, U9.13 (DP1_CC2)
USBH_1_DN: J3.A7 (D-), J3.B7 (D-), U9.6 (USB2DN_DM1/PRT_DIS_M1), U16.4 (IO3)
USBH_1_DP: J3.A6 (D+), J3.B6 (D+), U9.5 (USB2DN_DP1/PRT_DIS_P1), U16.5 (IO4)
USBH_2A_RXN: J14.B10 (RX1-), U9.35 (USB3DN_RXDM2A), U19.1 (IO1)
USBH_2A_RXP: J14.B11 (RX1+), U9.34 (USB3DN_RXDP2A), U19.2 (IO2)
USBH_2A_TXN: C90.2, U9.32 (USB3DN_TXDM2A)
USBH_2A_TXP: C92.2, U9.31 (USB3DN_TXDP2A)
USBH_2B_RXN: J14.A10 (RX2-), U9.40 (USB3DN_TXDM2B), U21.1 (IO1)
USBH_2B_RXP: J14.A11 (RX2+), U9.39 (USB3DN_TXDP2B), U21.2 (IO2)
USBH_2B_TXN: C91.2, U9.43 (USB3DN_RXDM2B)
USBH_2B_TXP: C93.2, U9.42 (USB3DN_RXDP2B)
USBH_2_CC1: R101.1, U9.27 (DP2_CC1)
USBH_2_CC2: R102.1, U9.28 (DP2_CC2)
USBH_2_DN: J14.A7 (D-), J14.B7 (D-), U9.30 (USB2DN_DM2/PRT_DIS_M2), U15.4 (IO3)
USBH_2_DP: J14.A6 (D+), J14.B6 (D+), U9.29 (USB2DN_DP2/PRT_DIS_P2), U15.5 (IO4)
USBH_3_DN: J6.2, U9.15 (USB2DN_DM3/PRT_DIS_M3)
USBH_3_DP: J6.3, U9.14 (USB2DN_DP3/PRT_DIS_P3)
USBH_4_DN: J12.9, U9.38 (USB2DN_DM4/PRT_DIS_M4)
USBH_4_DP: J12.7, U9.37 (USB2DN_DP4/PRT_DIS_P4)
USB_SRC_EN: U12.4 (EN)
USB_VBUS: D11.2 (A), J14.A4 (VBUS), J14.A9 (VBUS), J14.B4 (VBUS), J14.B9 (VBUS), U12.1 (OUT), U23.2 (VBUS)
VCC: C2.1, C4.1, C5.1, C7.1, C8.1, D2.1 (K), J1.1, J1.2, R19.2, R21.2, U2.3 (IN), U5.7 (VIN), U6.7 (VIN)
VCHG: D11.1 (K), J1.3, J1.4
~DISP_RESET: J13.24
~STANDBY_SHDN: R28.2, U2.5 (~SHDN), U7.3 (LBO)
~USBH_RESET: R5.2, R69.1, R70.2, U1.131 (USB_HUB_RESET)

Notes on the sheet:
Temp monitor?
Power Rails
These are OK, unclear why inconsistent pin numbering in symbol
Backlight is digitally controlled
consider: ANX7580 eDP -> DSI to integrate LS1028A
PERp1
PETp1
or: ON SEMI NCV1117ST18T3G
PERp3
TODO: decouple
TODO: voltages!
SSD M.2 Card Slot
LM3674MFX-1.2/NOPB
Realtime Clock
Optional 1Gb Ethernet
MIPI-DSI / Display Connector
TODO
SOURCE
GPIO43
TODO: we could supply 5V on VCONN
Keystone 2998 C238096
works only with NXP: optional internal USB connection RP/IMX
UART to KBD
Charger Interface
TODO: confirm
PERn2
TODO: confirm pinout!
TODO: Shield?
JDI LT070ME05000
PETp3
1.25mm pitch Molex Picoblade JST GH?
Power to charger
Status LED
disable battery charging
or: Heling MT24-S1T1
USB Hub
4.5-24V
M Key 42H M.2
PERp2
iX Industrial 10B-1

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

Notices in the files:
pocket-reform-keyboard-fw/pocket-hid/src/main.c:
SPDX-License-Identifier: GPL-3.0-or-later
Copyright 2021-2024 MNT Research GmbH (mntre.com)
Copyright 2019 Ha Thach (tinyusb.org)
